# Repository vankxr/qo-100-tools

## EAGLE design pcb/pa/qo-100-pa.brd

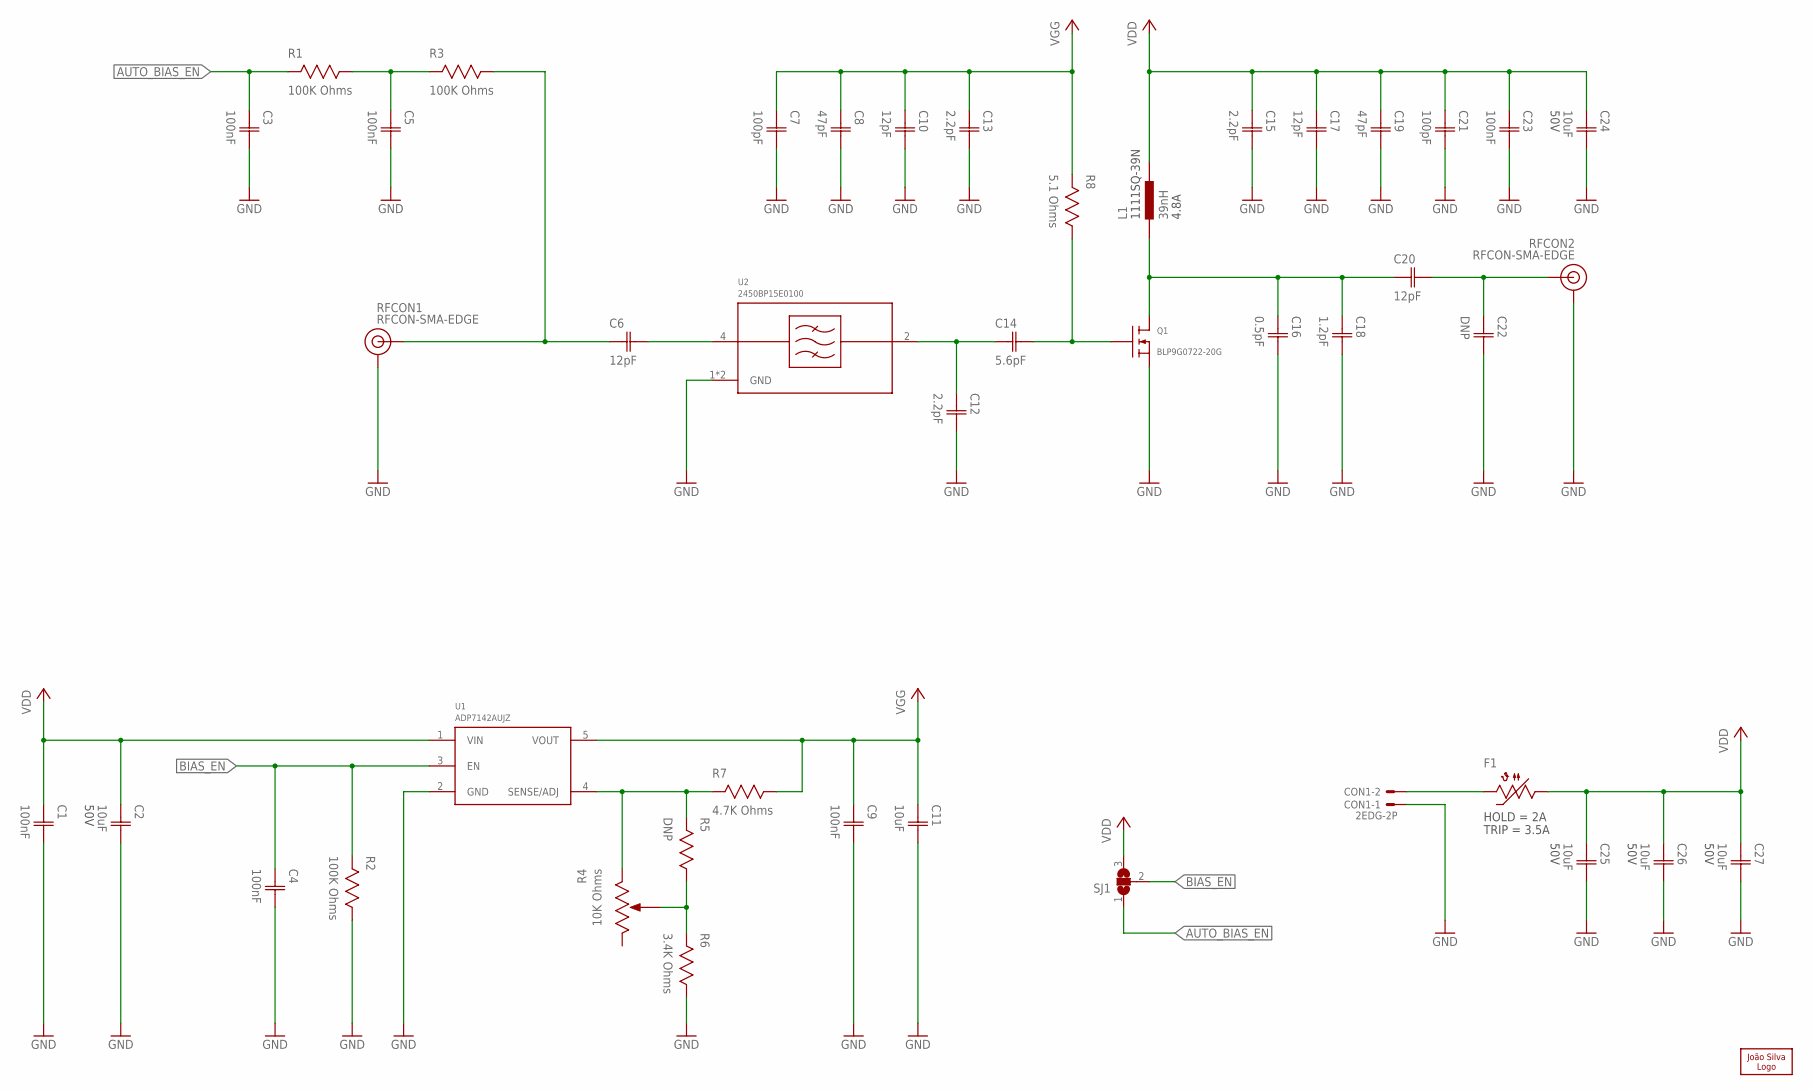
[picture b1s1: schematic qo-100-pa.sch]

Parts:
C1, C3, C4, C5, C9, C23: 100nF; CAP0603
C2, C24, C25, C26, C27: 10uF; CAP1206; VOLTAGE 50V
C6, C10, C17, C20: 12pF; CAP0603
C7, C21: 100pF; CAP0603
C8, C19: 47pF; CAP0603
C11: 10uF; CAP0603
C12, C13, C15: 2.2pF; CAP0603
C14: 5.6pF; CAP0603
C16: 0.5pF; CAP0603
C18: 1.2pF; CAP0603
C22: DNP; CAP0603
CON1: 2EDG-2P
F1: PTC1206; 1206
L1: 39nH; 1111SQ
LOGO1: JS-10MM; JS_10MM
Q1: BLP9G0722-20G; SOT1483-1
R1, R2, R3: 100K Ohms; RES0603
R4: 10K Ohms; POT3MM
R5: DNP; RES0603
R6: 3.4K Ohms; RES0603
R7: 4.7K Ohms; RES0603
R8: 5.1 Ohms; RES0603
RFCON1, RFCON2: RFCON-SMA-EDGE; SMA-EDGE
SJ1: SJ2S; SJ2_S
U1: ADP7142AUJZ; SOT23-5
U2: 2450BP15E0100

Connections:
AUTO_BIAS_EN: C3.1 (C1), R1.2, SJ1.1
BIAS_EN: C4.1 (C1), R2.2, SJ1.2, U1.3 (EN)
GND: C1.2 (C2), C2.2 (C2), C3.2 (C2), C4.2 (C2), C5.2 (C2), C7.2 (C2), C8.2 (C2), C9.2 (C2), C10.2 (C2), C11.2 (C2), C12.2 (C2), C13.2 (C2), C15.2 (C2), C16.2 (C2), C17.2 (C2), C18.2 (C2), C19.2 (C2), C21.2 (C2), C22.2 (C2), C23.2 (C2), C24.2 (C2), C25.2 (C2), C26.2 (C2), C27.2 (C2), CON1.P$1, Q1.3@0 (S), Q1.3@1 (S), Q1.3@2 (S), R2.1, R6.1, RFCON1.GND@0 (GND), RFCON1.GND@1 (GND), RFCON1.GND@2 (GND), RFCON1.GND@3 (GND), RFCON2.GND@0 (GND), RFCON2.GND@1 (GND), RFCON2.GND@2 (GND), RFCON2.GND@3 (GND), U1.2 (GND), U2.1 (GND), U2.3 (GND)
unnamed: CON1.P$2, F1.2
unnamed: C14.2 (C2), Q1.2 (G), R8.1
unnamed: C16.1 (C1), C18.1 (C1), C20.1 (C1), L1.1, Q1.1 (D)
unnamed: C20.2 (C2), C22.1 (C1), RFCON2.SIG (SIGNAL)
unnamed: C12.1 (C1), C14.1 (C1), U2.2 (RFOUT)
unnamed: C6.2 (C2), U2.4 (RFIN)
unnamed: C5.1 (C1), R1.1, R3.2
unnamed: R4.1 (CCW), R5.2, R7.2, U1.4 (SENSE/ADJ)
unnamed: R4.2 (WIPER), R5.1, R6.2
unnamed: C6.1 (C1), R3.1, RFCON1.SIG (SIGNAL)
VDD: C1.1 (C1), C2.1 (C1), C15.1 (C1), C17.1 (C1), C19.1 (C1), C21.1 (C1), C23.1 (C1), C24.1 (C1), C25.1 (C1), C26.1 (C1), C27.1 (C1), F1.1, L1.2, SJ1.3, U1.1 (VIN)
VGG: C7.1 (C1), C8.1 (C1), C9.1 (C1), C10.1 (C1), C11.1 (C1), C13.1 (C1), R7.1, R8.2, U1.5 (VOUT)

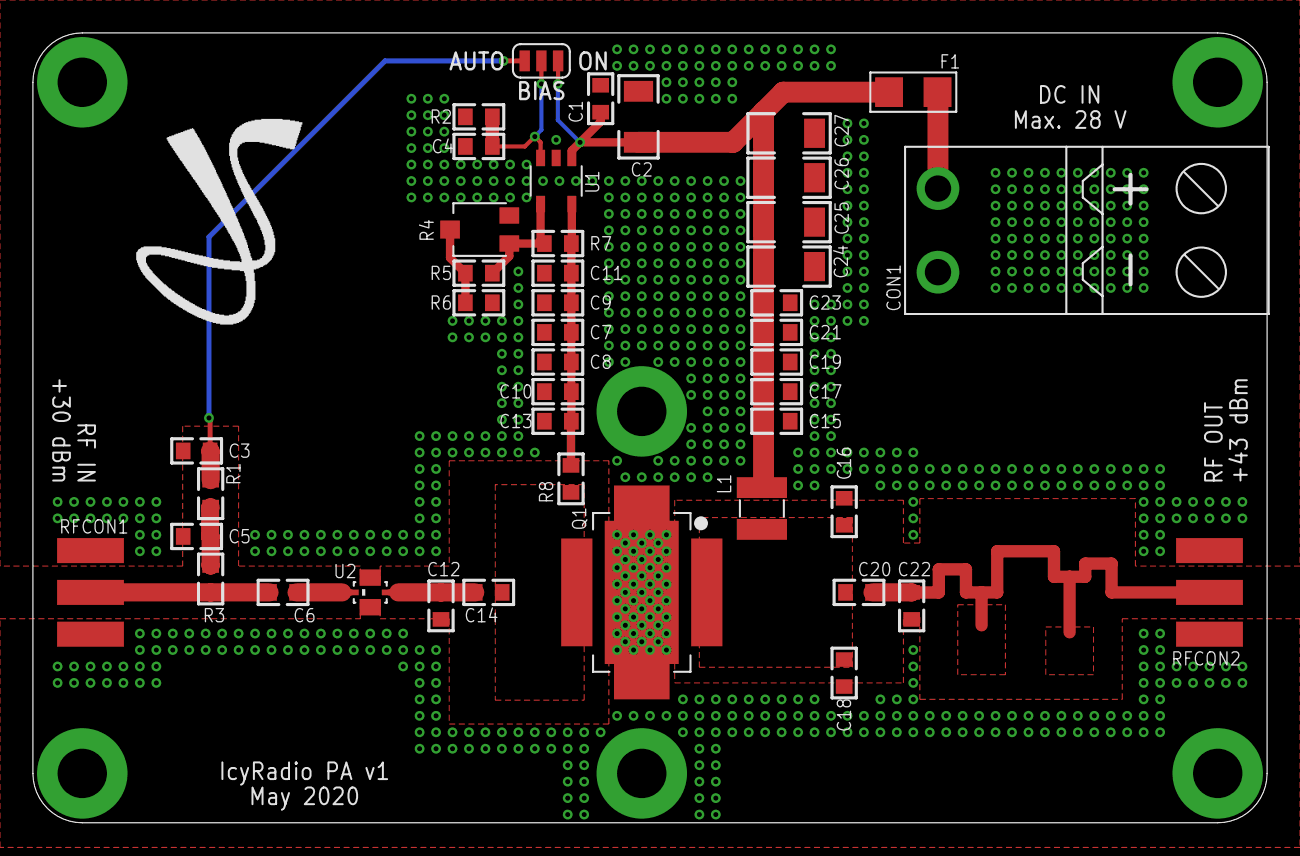
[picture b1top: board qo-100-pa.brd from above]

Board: 2 copper layers, 75.0 x 48.0 mm, 45 parts (0 on the bottom side), 15 nets.

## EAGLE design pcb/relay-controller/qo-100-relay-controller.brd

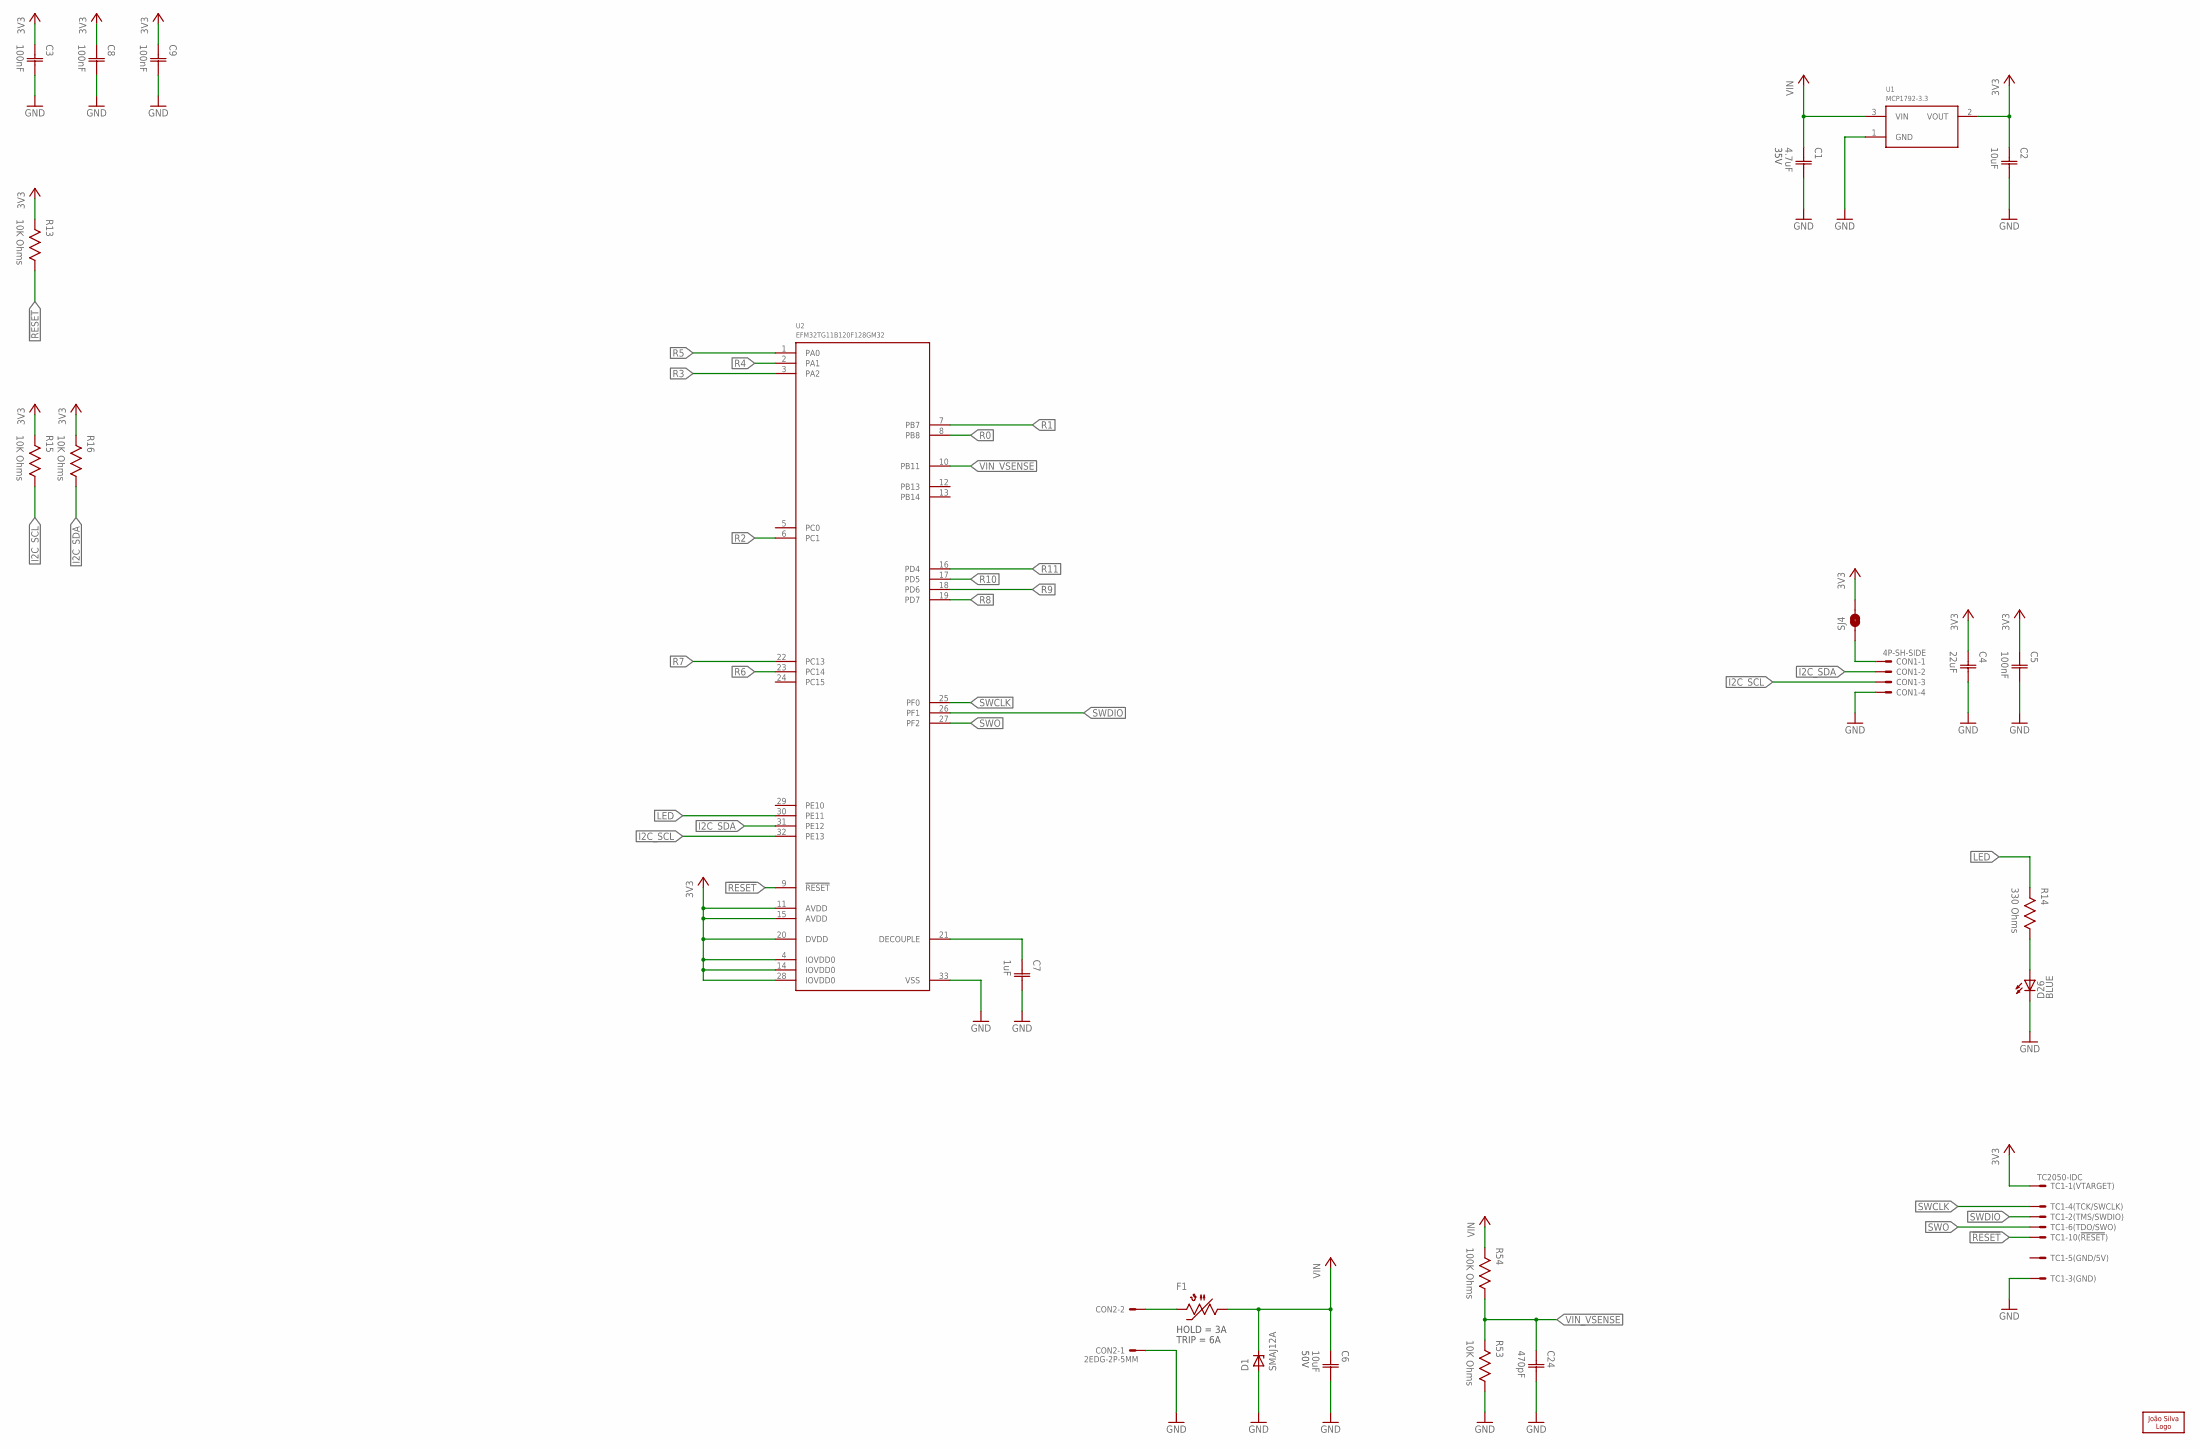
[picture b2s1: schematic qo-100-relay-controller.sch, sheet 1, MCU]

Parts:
C1: 4.7uF; CAP0603; VOLTAGE 35V
C2: 10uF; CAP0603
C3, C5, C8, C9: 100nF; CAP0603
C4: 22uF; CAP1206
C6: 10uF; CAP1206; VOLTAGE 50V
C7: 1uF; CAP0603
C24: 470pF; CAP0603
CON1: 4P-SH-SIDE; SH-04-SIDE
CON2: 2EDG-2P-5MM
D1: SMAJ12A; DO214AC
D26: LED0603; 0603
F1: 2.6A Hold; 1206
LOGO1: JS-5MM; JS_5MM
R13, R15, R16, R53: 10K Ohms; RES0603
R14: 330 Ohms; RES0603
R54: 100K Ohms; RES0603
SJ4: SJS; SJ_S
TC1: TC2050-IDC
U1: MCP1792-3.3; SOT23
U2: EFM32TG11B120F128GM32; QFN32_0.5P_TG

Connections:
3V3: C2.1 (C1), C3.1 (C1), C4.1 (C1), C5.1 (C1), C8.1 (C1), C9.1 (C1), R13.2, R15.2, R16.2, SJ4.2, TC1.1, U1.2 (VOUT), U2.4 (IOVDD0), U2.11 (AVDD), U2.14 (IOVDD0), U2.15 (AVDD), U2.20 (DVDD), U2.28 (IOVDD0); also elsewhere on the board
!RESET: R13.1, TC1.10, U2.9 (!RESET)
GND: C1.2 (C2), C2.2 (C2), C3.2 (C2), C4.2 (C2), C5.2 (C2), C6.2 (C2), C7.2 (C2), C8.2 (C2), C9.2 (C2), C24.2 (C2), CON1.4, CON2.P$1, D1.A, D26.C, R53.1, TC1.3, U1.1 (GND), U2.33 (VSS); also elsewhere on the board
I2C_SCL: CON1.3, R15.1, U2.32 (PE13)
I2C_SDA: CON1.2, R16.1, U2.31 (PE12)
LED: R14.2, U2.30 (PE11)
unnamed: CON1.1, SJ4.1
unnamed: C7.1 (C1), U2.21 (DECOUPLE)
unnamed: D26.A, R14.1
unnamed: CON2.P$2, F1.2
R0: U2.8 (PB8); also elsewhere on the board
R1: U2.7 (PB7); also elsewhere on the board
R2: U2.6 (PC1); also elsewhere on the board
R3: U2.3 (PA2); also elsewhere on the board
R4: U2.2 (PA1); also elsewhere on the board
R5: U2.1 (PA0); also elsewhere on the board
R6: U2.23 (PC14); also elsewhere on the board
R7: U2.22 (PC13); also elsewhere on the board
R8: U2.19 (PD7); also elsewhere on the board
R9: U2.18 (PD6); also elsewhere on the board
R10: U2.17 (PD5); also elsewhere on the board
R11: U2.16 (PD4); also elsewhere on the board
SWCLK: TC1.4, U2.25 (PF0)
SWDIO: TC1.2, U2.26 (PF1)
SWO: TC1.6, U2.27 (PF2)
VIN: C1.1 (C1), C6.1 (C1), D1.C, F1.1, R54.2, U1.3 (VIN); also elsewhere on the board
VIN_VSENSE: C24.1 (C1), R53.2, R54.1, U2.10 (PB11)

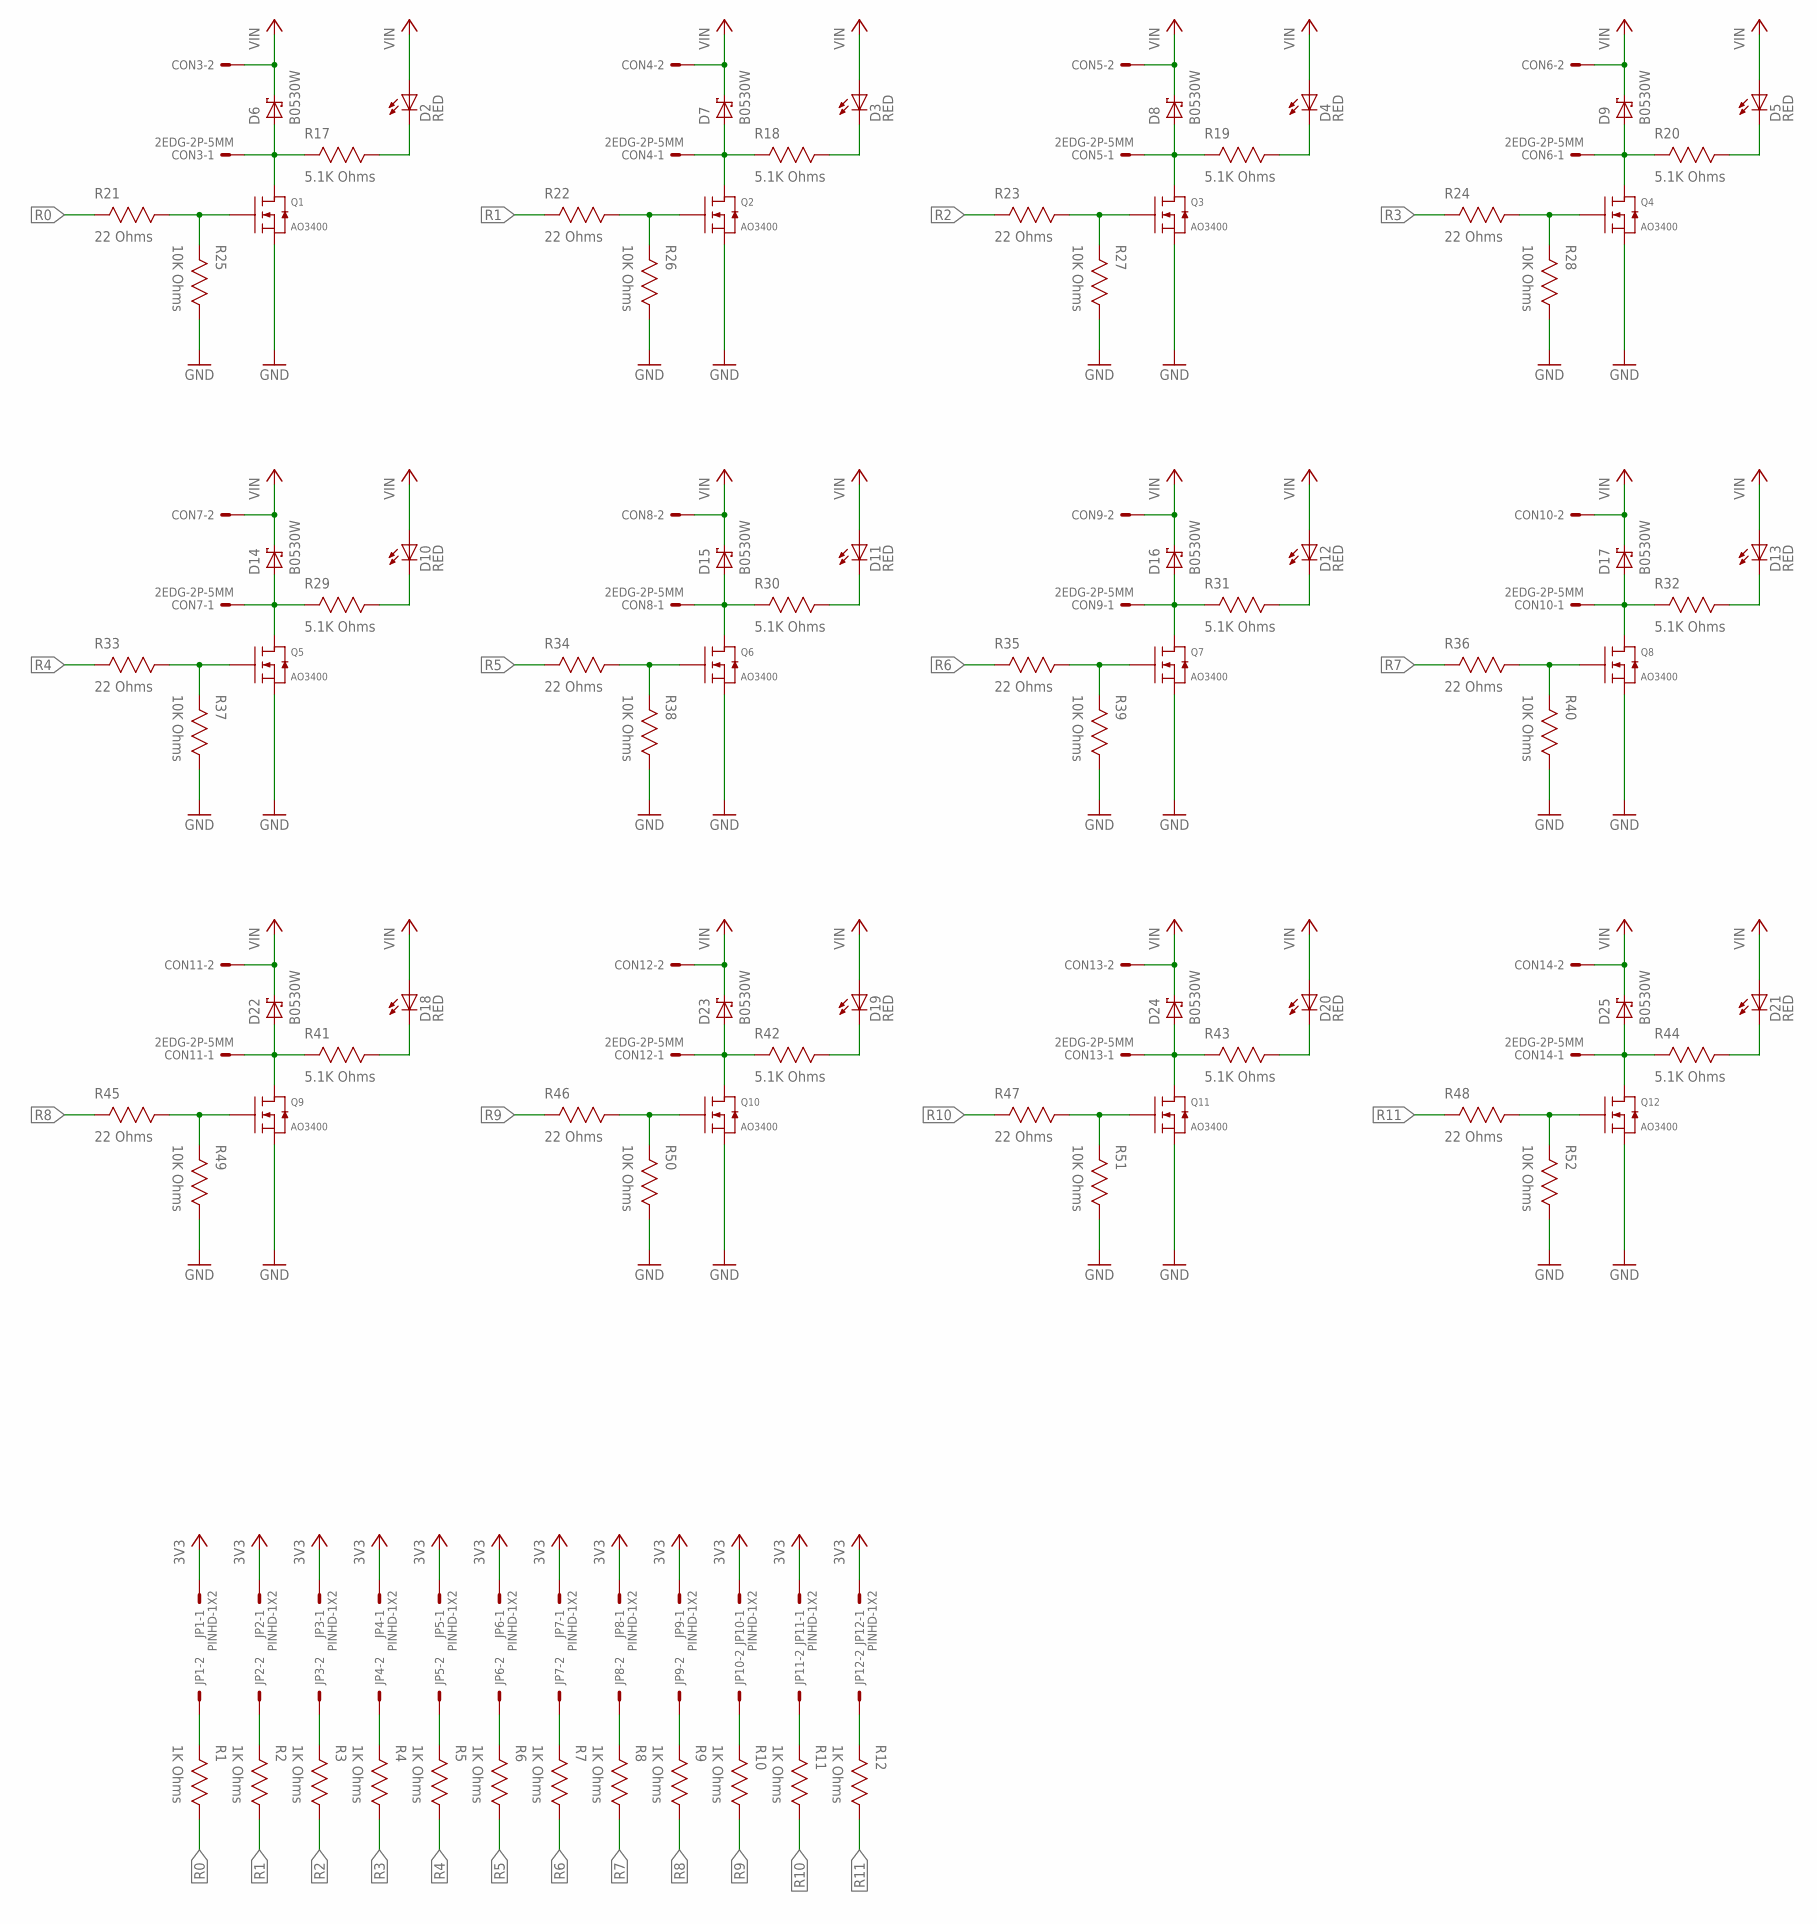
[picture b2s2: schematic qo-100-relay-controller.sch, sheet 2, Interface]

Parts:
CON3, CON4, CON5, CON6, CON7, CON8, CON9, CON10, CON11, CON12, CON13, CON14: 2EDG-2P-5MM
D2, D3, D4, D5, D10, D11, D12, D13, D18, D19, D20, D21: LED0603; 0603
D6, D7, D8, D9, D14, D15, D16, D17, D22, D23, D24, D25: B0530W; SOD-123
JP1, JP2, JP3, JP4, JP5, JP6, JP7, JP8, JP9, JP10, JP11, JP12: PINHD-1X2; 1X02
Q1, Q2, Q3, Q4, Q5, Q6, Q7, Q8, Q9, Q10, Q11, Q12: AO3400; SOT23
R1, R2, R3, R4, R5, R6, R7, R8, R9, R10, R11, R12: 1K Ohms; RES0603
R17, R18, R19, R20, R29, R30, R31, R32, R41, R42, R43, R44: 5.1K Ohms; RES0603
R21, R22, R23, R24, R33, R34, R35, R36, R45, R46, R47, R48: 22 Ohms; RES0603
R25, R26, R27, R28, R37, R38, R39, R40, R49, R50, R51, R52: 10K Ohms; RES0603

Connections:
3V3: JP1.1, JP2.1, JP3.1, JP4.1, JP5.1, JP6.1, JP7.1, JP8.1, JP9.1, JP10.1, JP11.1, JP12.1; also elsewhere on the board
GND: Q1.2 (S), Q2.2 (S), Q3.2 (S), Q4.2 (S), Q5.2 (S), Q6.2 (S), Q7.2 (S), Q8.2 (S), Q9.2 (S), Q10.2 (S), Q11.2 (S), Q12.2 (S), R25.1, R26.1, R27.1, R28.1, R37.1, R38.1, R39.1, R40.1, R49.1, R50.1, R51.1, R52.1; also elsewhere on the board
unnamed: JP1.2, R1.2
unnamed: JP2.2, R2.2
unnamed: JP3.2, R3.2
unnamed: JP4.2, R4.2
unnamed: JP5.2, R5.2
unnamed: JP6.2, R6.2
unnamed: JP7.2, R7.2
unnamed: JP8.2, R8.2
unnamed: JP9.2, R9.2
unnamed: JP10.2, R10.2
unnamed: JP11.2, R11.2
unnamed: JP12.2, R12.2
unnamed: Q1.1 (G), R21.1, R25.2
unnamed: CON3.P$1, D6.A, Q1.3 (D), R17.2
unnamed: D2.C, R17.1
unnamed: Q2.1 (G), R22.1, R26.2
unnamed: CON4.P$1, D7.A, Q2.3 (D), R18.2
unnamed: D3.C, R18.1
unnamed: Q3.1 (G), R23.1, R27.2
unnamed: CON5.P$1, D8.A, Q3.3 (D), R19.2
unnamed: D4.C, R19.1
unnamed: Q4.1 (G), R24.1, R28.2
unnamed: CON6.P$1, D9.A, Q4.3 (D), R20.2
unnamed: D5.C, R20.1
unnamed: Q5.1 (G), R33.1, R37.2
unnamed: CON7.P$1, D14.A, Q5.3 (D), R29.2
unnamed: D10.C, R29.1
unnamed: Q6.1 (G), R34.1, R38.2
unnamed: CON8.P$1, D15.A, Q6.3 (D), R30.2
unnamed: D11.C, R30.1
unnamed: Q7.1 (G), R35.1, R39.2
unnamed: CON9.P$1, D16.A, Q7.3 (D), R31.2
unnamed: D12.C, R31.1
unnamed: Q8.1 (G), R36.1, R40.2
unnamed: CON10.P$1, D17.A, Q8.3 (D), R32.2
unnamed: D13.C, R32.1
unnamed: Q9.1 (G), R45.1, R49.2
unnamed: CON11.P$1, D22.A, Q9.3 (D), R41.2
unnamed: D18.C, R41.1
unnamed: Q10.1 (G), R46.1, R50.2
unnamed: CON12.P$1, D23.A, Q10.3 (D), R42.2
unnamed: D19.C, R42.1
unnamed: Q11.1 (G), R47.1, R51.2
unnamed: CON13.P$1, D24.A, Q11.3 (D), R43.2
unnamed: D20.C, R43.1
unnamed: Q12.1 (G), R48.1, R52.2
unnamed: CON14.P$1, D25.A, Q12.3 (D), R44.2
unnamed: D21.C, R44.1
R0: R1.1, R21.2; also elsewhere on the board
R1: R2.1, R22.2; also elsewhere on the board
R2: R3.1, R23.2; also elsewhere on the board
R3: R4.1, R24.2; also elsewhere on the board
R4: R5.1, R33.2; also elsewhere on the board
R5: R6.1, R34.2; also elsewhere on the board
R6: R7.1, R35.2; also elsewhere on the board
R7: R8.1, R36.2; also elsewhere on the board
R8: R9.1, R45.2; also elsewhere on the board
R9: R10.1, R46.2; also elsewhere on the board
R10: R11.1, R47.2; also elsewhere on the board
R11: R12.1, R48.2; also elsewhere on the board
VIN: CON3.P$2, CON4.P$2, CON5.P$2, CON6.P$2, CON7.P$2, CON8.P$2, CON9.P$2, CON10.P$2, CON11.P$2, CON12.P$2, CON13.P$2, CON14.P$2, D2.A, D3.A, D4.A, D5.A, D6.C, D7.C, D8.C, D9.C, D10.A, D11.A, D12.A, D13.A, D14.C, D15.C, D16.C, D17.C, D18.A, D19.A, D20.A, D21.A, D22.C, D23.C, D24.C, D25.C; also elsewhere on the board

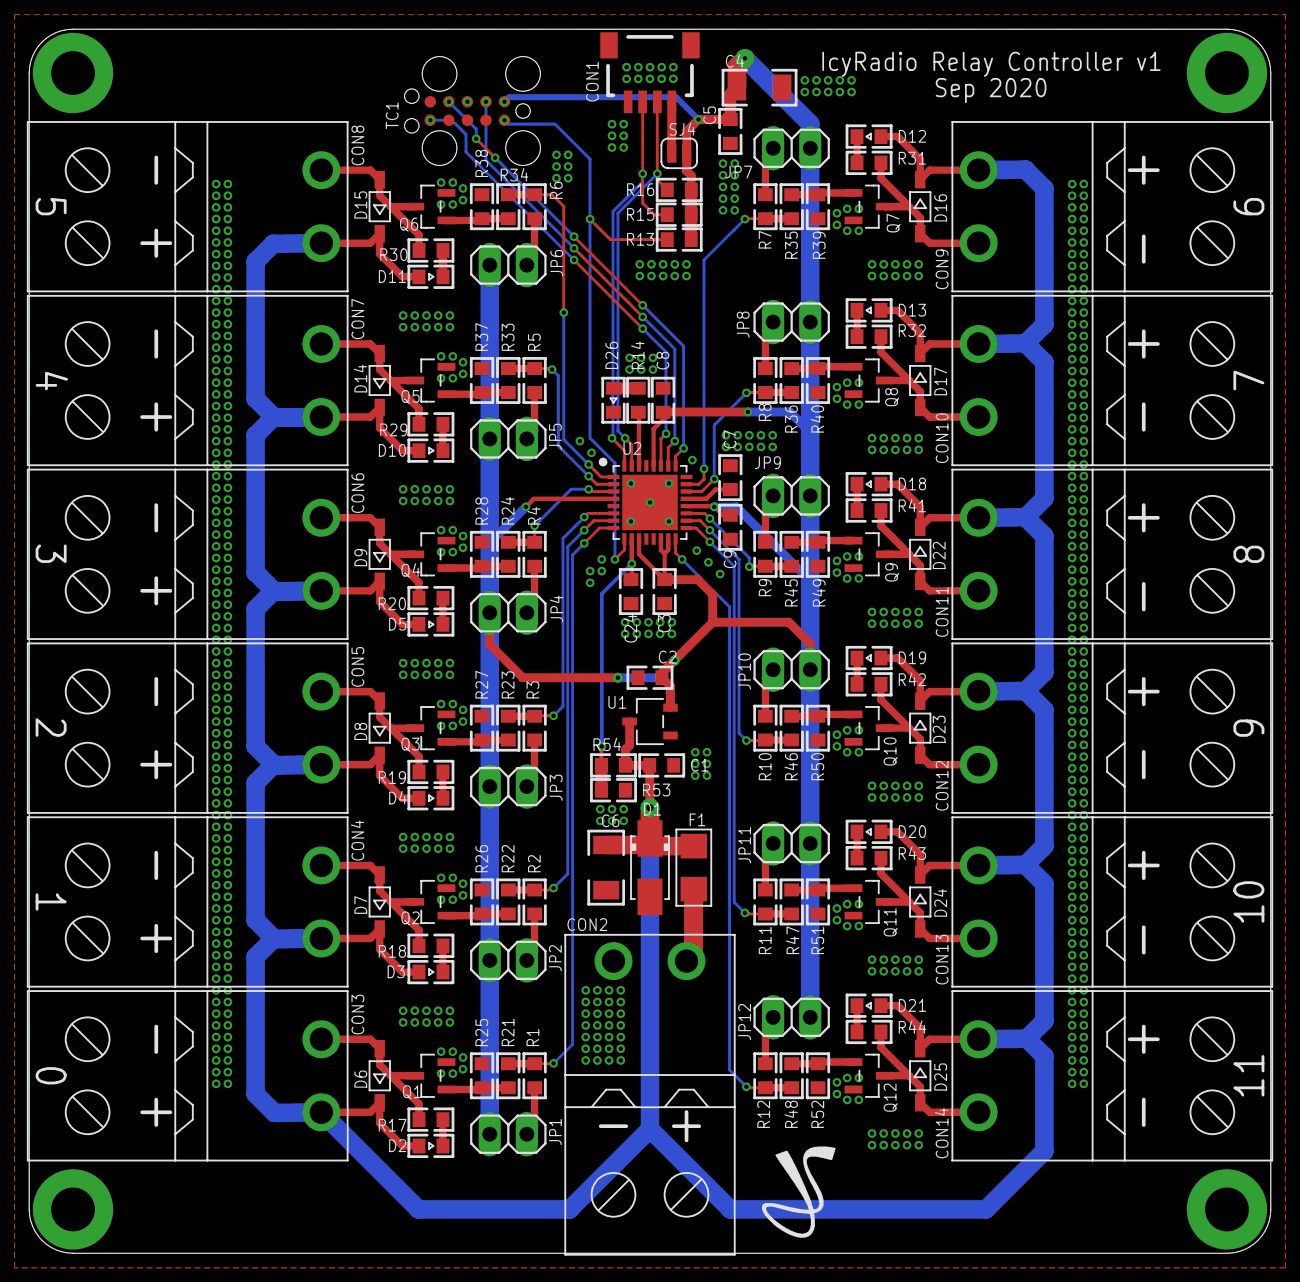
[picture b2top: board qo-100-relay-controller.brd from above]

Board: 2 copper layers, 85.0 x 83.8 mm, 134 parts (0 on the bottom side), 75 nets.

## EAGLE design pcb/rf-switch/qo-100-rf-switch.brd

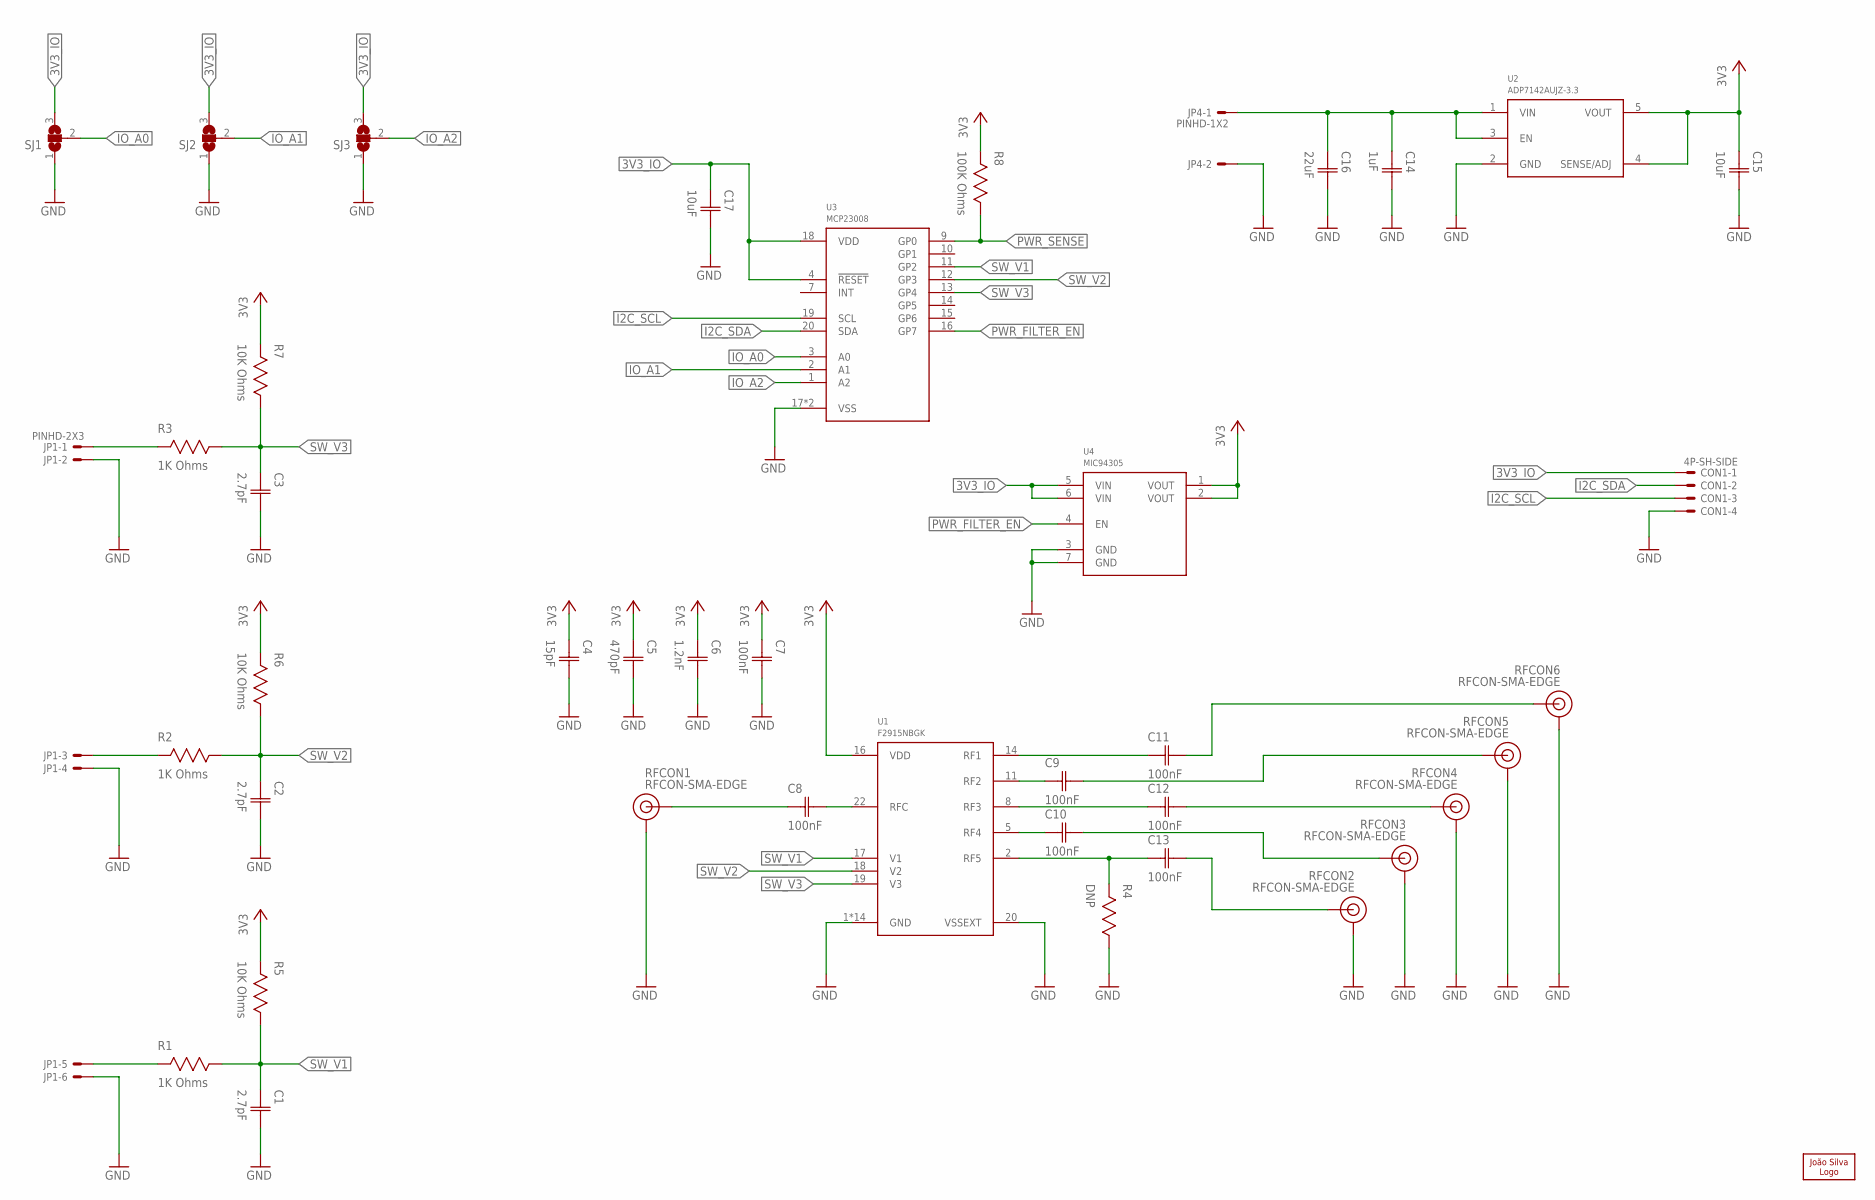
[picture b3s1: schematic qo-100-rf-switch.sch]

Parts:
C1, C2, C3: 2.7pF; CAP0603
C4: 15pF; CAP0603
C5: 470pF; CAP0603
C6: 1.2nF; CAP0603
C7, C8, C9, C10, C11, C12, C13: 100nF; CAP0603
C14: 1uF; CAP0603
C15, C17: 10uF; CAP0603
C16: 22uF; CAP1206
CON1: 4P-SH-SIDE; SH-04-SIDE
JP1: PINHD-2X3; 2X03
JP4: PINHD-1X2; 1X02
LOGO1: JS-5MM; JS_5MM
R1, R2, R3: 1K Ohms; RES0603
R4: DNP; RES0603
R5, R6, R7: 10K Ohms; RES0603
R8: 100K Ohms; RES0603
RFCON1, RFCON2, RFCON3, RFCON4, RFCON5, RFCON6: RFCON-SMA-EDGE; SMA-EDGE
SJ1, SJ2, SJ3: SJ2S; SJ2_S
U1: F2915NBGK; QFN24
U2: ADP7142AUJZ-3.3; SOT23-5
U3: MCP23008; QFN20
U4: MIC94305; DFN6

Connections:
3V3: C4.1 (C1), C5.1 (C1), C6.1 (C1), C7.1 (C1), C15.1 (C1), R5.2, R6.2, R7.2, R8.2, U1.16 (VDD), U2.4 (SENSE/ADJ), U2.5 (VOUT), U4.1 (VOUT), U4.2 (VOUT)
3V3_IO: C17.1 (C1), CON1.1, SJ1.3, SJ2.3, SJ3.3, U3.4 (!RESET), U3.18 (VDD), U4.5 (VIN), U4.6 (VIN)
GND: C1.2 (C2), C2.2 (C2), C3.2 (C2), C4.2 (C2), C5.2 (C2), C6.2 (C2), C7.2 (C2), C14.2 (C2), C15.2 (C2), C16.2 (C2), C17.2 (C2), CON1.4, JP1.2, JP1.4, JP1.6, JP4.2, R4.1, RFCON1.GND@0 (GND), RFCON1.GND@1 (GND), RFCON1.GND@2 (GND), RFCON1.GND@3 (GND), RFCON2.GND@0 (GND), RFCON2.GND@1 (GND), RFCON2.GND@2 (GND), RFCON2.GND@3 (GND), RFCON3.GND@0 (GND), RFCON3.GND@1 (GND), RFCON3.GND@2 (GND), RFCON3.GND@3 (GND), RFCON4.GND@0 (GND), RFCON4.GND@1 (GND), RFCON4.GND@2 (GND), RFCON4.GND@3 (GND), RFCON5.GND@0 (GND), RFCON5.GND@1 (GND), RFCON5.GND@2 (GND), RFCON5.GND@3 (GND), RFCON6.GND@0 (GND), RFCON6.GND@1 (GND), RFCON6.GND@2 (GND), RFCON6.GND@3 (GND), SJ1.1, SJ2.1, SJ3.1, U1.1 (GND), U1.3 (GND), U1.4 (GND), U1.6 (GND), U1.7 (GND), U1.9 (GND), U1.10 (GND), U1.12 (GND), U1.13 (GND), U1.15 (GND), U1.20 (VSSEXT), U1.21 (GND), U1.23 (GND), U1.24 (GND), U1.25 (GND), U2.2 (GND), U3.17 (VSS), U3.PAD (VSS), U4.3 (GND), U4.7 (GND)
I2C_SCL: CON1.3, U3.19 (SCL)
I2C_SDA: CON1.2, U3.20 (SDA)
IO_A0: SJ1.2, U3.3 (A0)
IO_A1: SJ2.2, U3.2 (A1)
IO_A2: SJ3.2, U3.1 (A2)
unnamed: C8.1 (C1), RFCON1.SIG (SIGNAL)
unnamed: C8.2 (C2), U1.22 (RFC)
unnamed: C13.1 (C1), R4.2, U1.2 (RF5)
unnamed: C10.1 (C1), U1.5 (RF4)
unnamed: C12.1 (C1), U1.8 (RF3)
unnamed: C9.1 (C1), U1.11 (RF2)
unnamed: C11.1 (C1), U1.14 (RF1)
unnamed: C13.2 (C2), RFCON2.SIG (SIGNAL)
unnamed: C10.2 (C2), RFCON3.SIG (SIGNAL)
unnamed: C12.2 (C2), RFCON4.SIG (SIGNAL)
unnamed: C9.2 (C2), RFCON5.SIG (SIGNAL)
unnamed: C11.2 (C2), RFCON6.SIG (SIGNAL)
unnamed: JP1.1, R3.2
unnamed: JP1.3, R2.2
unnamed: JP1.5, R1.2
unnamed: C14.1 (C1), C16.1 (C1), JP4.1, U2.1 (VIN), U2.3 (EN)
PWR_FILTER_EN: U3.16 (GP7), U4.4 (EN)
PWR_SENSE: R8.1, U3.9 (GP0)
SW_V1: C1.1 (C1), R1.1, R5.1, U1.17 (V1), U3.11 (GP2)
SW_V2: C2.1 (C1), R2.1, R6.1, U1.18 (V2), U3.12 (GP3)
SW_V3: C3.1 (C1), R3.1, R7.1, U1.19 (V3), U3.13 (GP4)

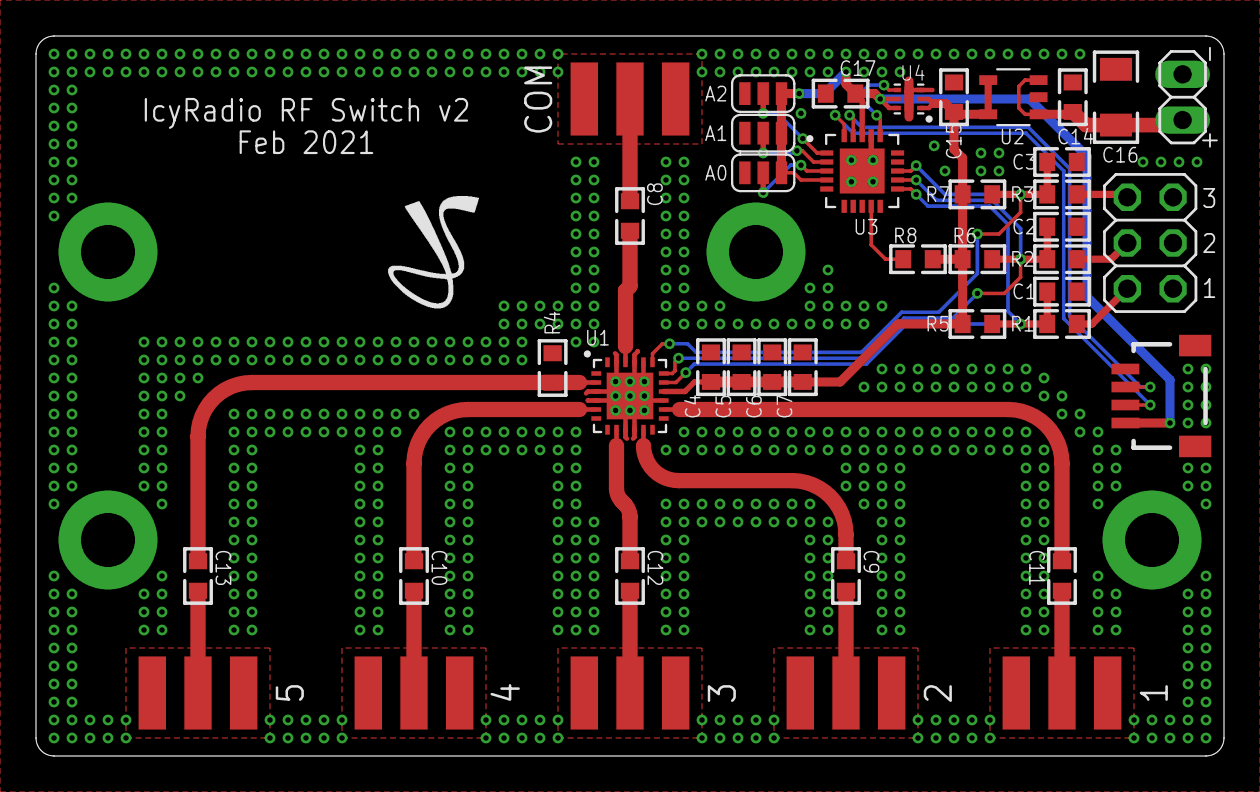
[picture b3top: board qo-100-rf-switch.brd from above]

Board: 2 copper layers, 66.0 x 40.0 mm, 42 parts (0 on the bottom side), 29 nets.
